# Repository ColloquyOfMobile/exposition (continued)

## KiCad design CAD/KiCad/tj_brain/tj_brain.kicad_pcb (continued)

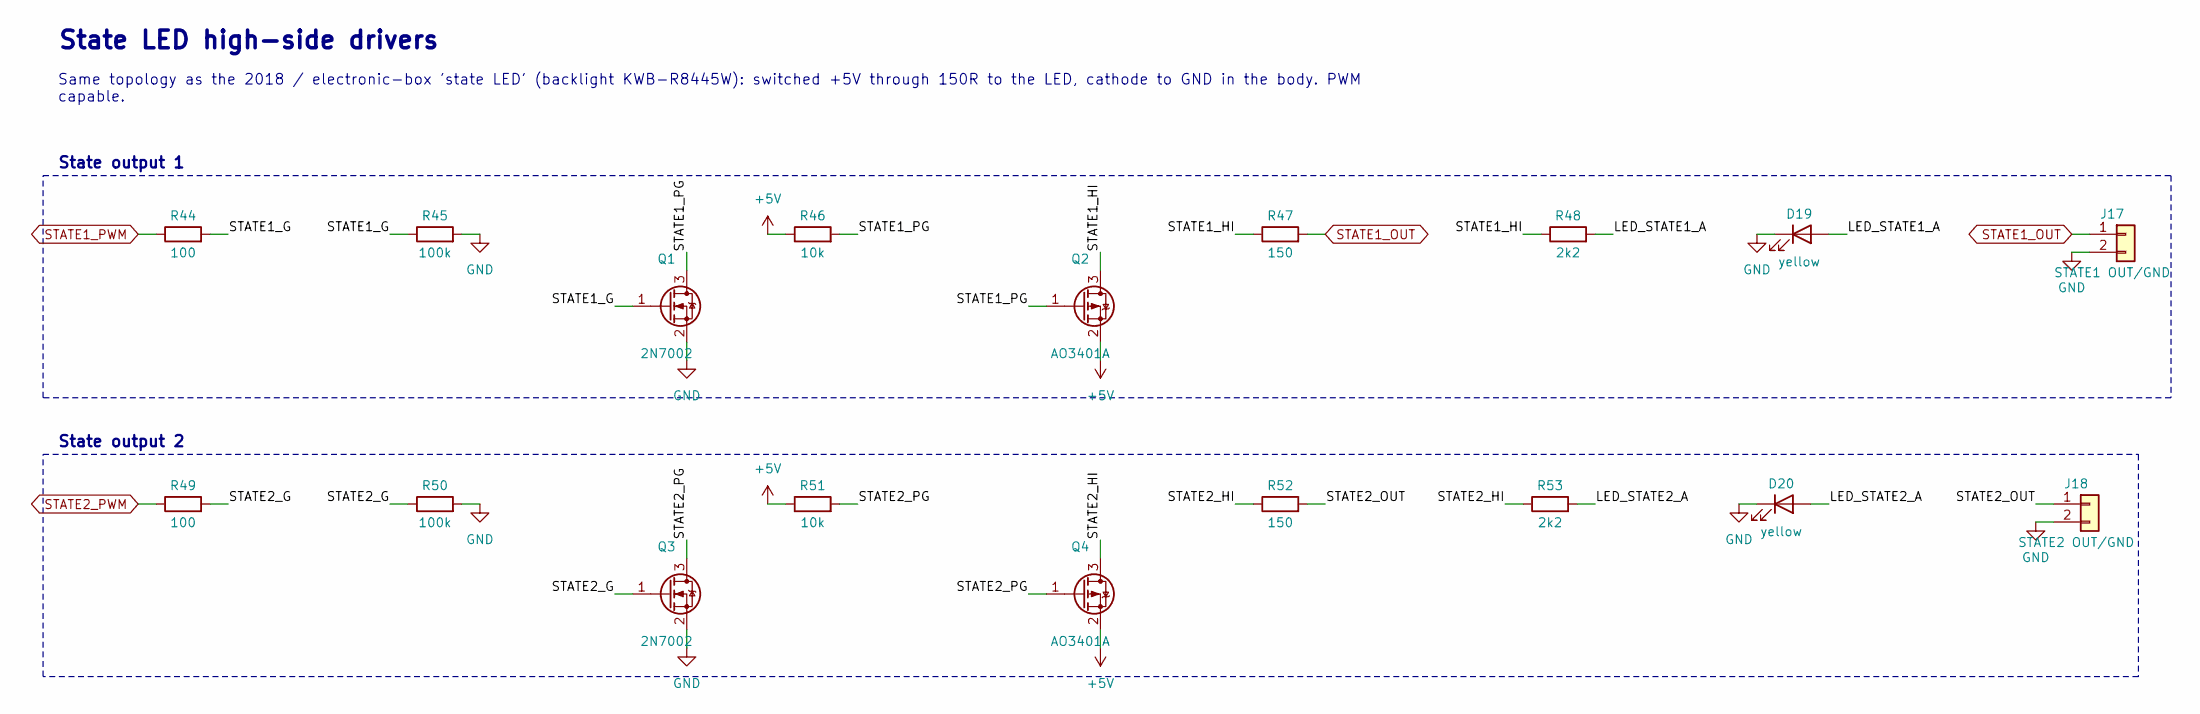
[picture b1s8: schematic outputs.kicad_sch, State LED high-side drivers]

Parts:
D19, D20: yellow; LED_0805_2012Metric_Pad1.15x1.40mm_HandSolder
J17: STATE1 OUT/GND; JST_XH_B2B-XH-A_1x02_P2.50mm_Vertical
J18: STATE2 OUT/GND; JST_XH_B2B-XH-A_1x02_P2.50mm_Vertical
Q1, Q3: 2N7002; SOT-23
Q2, Q4: AO3401A; SOT-23
R44, R49: 100; R_0805_2012Metric_Pad1.20x1.40mm_HandSolder
R45, R50: 100k; R_0805_2012Metric_Pad1.20x1.40mm_HandSolder
R46, R51: 10k; R_0805_2012Metric_Pad1.20x1.40mm_HandSolder
R47, R52: 150; R_1206_3216Metric_Pad1.30x1.75mm_HandSolder
R48, R53: 2k2; R_0805_2012Metric_Pad1.20x1.40mm_HandSolder

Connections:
+5V: Q2.2 (S), Q4.2 (S), R46.1, R51.1; also elsewhere on the board
GND: D19.1 (K), D20.1 (K), J17.2, J18.2, Q1.2 (S), Q3.2 (S), R45.2, R50.2; also elsewhere on the board
LED_STATE1_A: D19.2 (A), R48.2
LED_STATE2_A: D20.2 (A), R53.2
STATE1_G: Q1.1 (G), R44.2, R45.1
STATE1_HI: Q2.3 (D), R47.1, R48.1
STATE1_OUT: J17.1, R47.2; also elsewhere on the board
STATE1_PG: Q1.3 (D), Q2.1 (G), R46.2
STATE1_PWM: R44.1; also elsewhere on the board
STATE2_G: Q3.1 (G), R49.2, R50.1
STATE2_HI: Q4.3 (D), R52.1, R53.1
STATE2_OUT: J18.1, R52.2
STATE2_PG: Q3.3 (D), Q4.1 (G), R51.2
STATE2_PWM: R49.1; also elsewhere on the board

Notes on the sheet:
State LED high-side drivers
Same topology as the 2018 / electronic-box 'state LED' (backlight KWB-R8445W): switched +5V through 150R to the LED, cathode to GND in the body. PWM
capable.
State output 1
State output 2

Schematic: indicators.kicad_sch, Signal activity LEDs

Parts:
C25, C26: 100n; C_0805_2012Metric_Pad1.18x1.45mm_HandSolder
C27, C28, C29, C30, C31, C32, C33, C34: 47n; C_0805_2012Metric_Pad1.18x1.45mm_HandSolder
D21, D23, D25, D27, D29, D31, D33, D35: BAT54WS; D_SOD-323_HandSoldering
D22, D24, D26, D28: yellow; LED_0805_2012Metric_Pad1.15x1.40mm_HandSolder
D30, D32, D34, D36: orange; LED_0805_2012Metric_Pad1.15x1.40mm_HandSolder
J19: PROBE; PinHeader_1x01_P2.54mm_Vertical
R54: 100k; R_0805_2012Metric_Pad1.20x1.40mm_HandSolder
R55, R57, R58, R60, R61, R63, R64, R66, R67, R69, R70, R72, R73, R75, R78: 1k; R_0805_2012Metric_Pad1.20x1.40mm_HandSolder
R56, R59, R62, R65, R68, R71, R74, R77: 1M; R_0805_2012Metric_Pad1.20x1.40mm_HandSolder
R76: 4k7; R_0805_2012Metric_Pad1.20x1.40mm_HandSolder
U8, U9: 74HC14; SOIC-14_3.9x8.7mm_P1.27mm

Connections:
+3V3: C25.1, C26.1, R57.1, R60.1, R63.1, R66.1, R69.1, R71.2, R75.1, R78.1, U8.14 (VCC), U9.14 (VCC); also elsewhere on the board
AUDIO_PWM: R73.1; also elsewhere on the board
DXL_DIR: R67.1; also elsewhere on the board
DXL_RX: R70.1; also elsewhere on the board
GND: C25.2, C26.2, C27.2, C28.2, C29.2, C30.2, C31.2, C32.2, C33.2, C34.2, D32.1 (K), R54.2, R56.2, R59.2, R62.2, R65.2, R68.2, R74.2, R77.2, U8.7 (GND), U9.5, U9.7 (GND), U9.9, U9.11, U9.13; also elsewhere on the board
IND1_D: D21.2 (A), R55.2
IND1_K: D22.2 (A), R57.2
IND1_S: C27.1, D21.1 (K), R56.1, U8.1
IND1_Y: D22.1 (K), U8.2
IND2_D: D23.2 (A), R58.2
IND2_K: D24.2 (A), R60.2
IND2_S: C28.1, D23.1 (K), R59.1, U8.3
IND2_Y: D24.1 (K), U8.4
IND3_D: D25.2 (A), R61.2
IND3_K: D26.2 (A), R63.2
IND3_S: C29.1, D25.1 (K), R62.1, U8.5
IND3_Y: D26.1 (K), U8.6
IND4_D: D27.2 (A), R64.2
IND4_K: D28.2 (A), R66.2
IND4_S: C30.1, D27.1 (K), R65.1, U8.9
IND4_Y: D28.1 (K), U8.8
IND5_D: D29.2 (A), R67.2
IND5_K: D30.2 (A), R69.2
IND5_S: C31.1, D29.1 (K), R68.1, U8.11
IND5_Y: D30.1 (K), U8.10
IND6_D: D31.1 (K), R70.2
IND6_K: D32.2 (A), R72.2
IND6_S: C32.1, D31.2 (A), R71.1, U8.13
IND6_Y: R72.1, U8.12
IND7_D: D33.2 (A), R73.2
IND7_K: D34.2 (A), R75.2
IND7_S: C33.1, D33.1 (K), R74.1, U9.1
IND7_Y: D34.1 (K), U9.2
IND8_D: D35.2 (A), R76.2
IND8_K: D36.2 (A), R78.2
IND8_S: C34.1, D35.1 (K), R77.1, U9.3
IND8_Y: D36.1 (K), U9.4
NP1_3V: R55.1; also elsewhere on the board
NP2_3V: R58.1; also elsewhere on the board
NP3_3V: R61.1; also elsewhere on the board
NP4_3V: R64.1; also elsewhere on the board
PROBE: J19.1, R54.1, R76.1

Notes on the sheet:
Signal activity LEDs
Each signal is tapped through 1k + Schottky into 47n || 1M (~50 ms pulse stretcher) and drives a 74HC14 (3.3V) so that short NeoPixel / Dynamixel
bursts are visible. PROBE = free logic probe.
Schmitt inverters
Probe input
Indicator NP1
Indicator NP2
Indicator NP3
Indicator NP4
Indicator DXL TX
Indicator DXL BUS
Indicator TONE
Indicator PROBE

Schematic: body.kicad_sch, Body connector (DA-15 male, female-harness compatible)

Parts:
J20: BODY DA-15 male; DSUB-15_Male_Horizontal_P2.77x2.84mm_EdgePinOffset4.94mm_Ho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

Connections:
+5V_BODY: J20.15; also elsewhere on the board
+12V_BODY: J20.7; also elsewhere on the board
AUX_IN: J20.11 (P111); also elsewhere on the board
DXL_DATA: J20.14; also elsewhere on the board
GND: J20.0 (PAD), J20.8; also elsewhere on the board
LS1_IN: J20.5; also elsewhere on the board
LS2_IN: J20.1; also elsewhere on the board
LS3_IN: J20.2; also elsewhere on the board
LS4_IN: J20.3; also elsewhere on the board
MIC_IN: J20.6; also elsewhere on the board
NP1_OUT: J20.13; also elsewhere on the board
NP2_OUT: J20.9; also elsewhere on the board
SPK+: J20.12; also elsewhere on the board
SPK-: J20.4; also elsewhere on the board
STATE1_OUT: J20.10; also elsewhere on the board

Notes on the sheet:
Body connector (DA-15 male, female-harness compatible)
Pins 4,5,6,7,8,12,13,14,15 identical to the ZKM electronic box female D-subs (J1/J5), so existing female body harnesses plug in unchanged. Pins
1,2,3,9,10,11 add the male extras.
DA-15

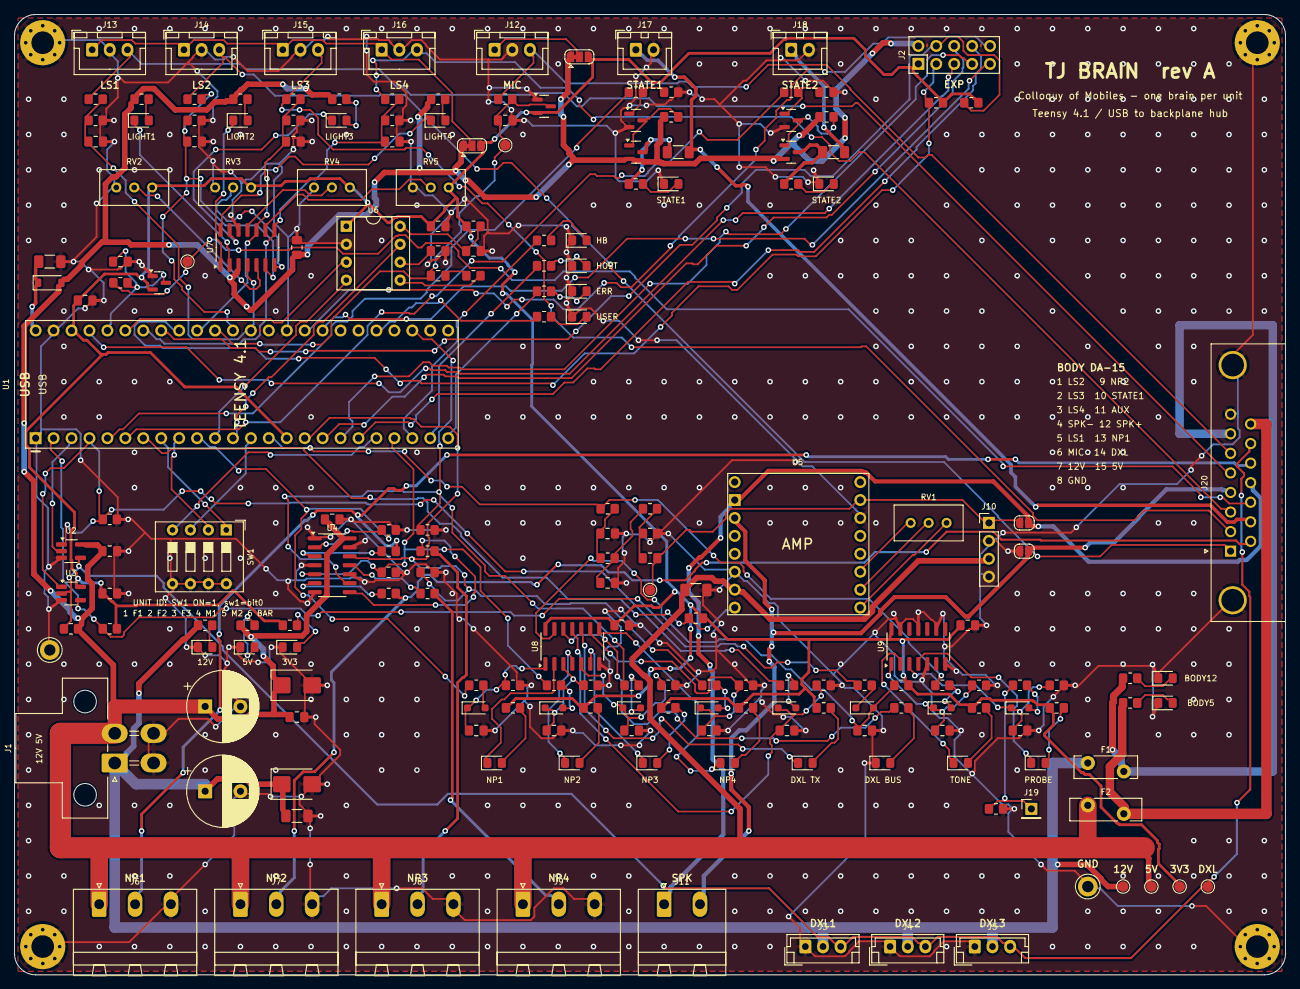
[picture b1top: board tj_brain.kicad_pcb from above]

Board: 2 copper layers, 180.0 x 136.0 mm, 206 parts (0 on the bottom side), 137 nets.

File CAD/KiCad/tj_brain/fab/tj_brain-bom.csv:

References,Qty,Value,Footprint,Manufacturer part / note,Populate,Description
C1,1,470u 25V,CP_Radial_D10.0mm_P5.00mm,,,
C2,1,100n,C_1206_3216Metric_Pad1.33x1.80mm_HandSolder,,,
C3,1,1000u 10V,CP_Radial_D10.0mm_P5.00mm,,,
"C4, C6, C7, C8, C9, C15, C16, C19, C25, C26",10,100n,C_0805_2012Metric_Pad1.18x1.45mm_HandSolder,,,
"C5, C13",2,10u,C_1206_3216Metric_Pad1.33x1.80mm_HandSolder,,,
"C10, C11",2,150n,C_0805_2012Metric_Pad1.18x1.45mm_HandSolder,,,
C12,1,1u,C_0805_2012Metric_Pad1.18x1.45mm_HandSolder,,,
C14,1,1n,C_0805_2012Metric_Pad1.18x1.45mm_HandSolder,,,
"C17, C20, C21, C22, C23, C24",6,10n,C_0805_2012Metric_Pad1.18x1.45mm_HandSolder,,,
C18,1,33p,C_0805_2012Metric_Pad1.18x1.45mm_HandSolder,,,
"C27, C28, C29, C30, C31, C32, C33, C34",8,47n,C_0805_2012Metric_Pad1.18x1.45mm_HandSolder,,,
D1,1,SMBJ15A,D_SMB,,,TVS 15V unidirectional
D2,1,SMBJ5.0A,D_SMB,,,TVS 5V unidirectional
D3,1,B5819W,D_SOD-123,,,Schottky 1A 40V; lets the Teensy VIN/VUSB link stay uncut
"D4, D7, D11",3,red,LED_0805_2012Metric_Pad1.15x1.40mm_HandSolder,,,
"D5, D6, D8, D9",4,green,LED_0805_2012Metric_Pad1.15x1.40mm_HandSolder,,,
D10,1,blue,LED_0805_2012Metric_Pad1.15x1.40mm_HandSolder,,,
"D12, D19, D20, D22, D24, D26, D28",7,yellow,LED_0805_2012Metric_Pad1.15x1.40mm_HandSolder,,,
"D13, D18",2,BAT54S,SOT-23,,,clamp 0..3.3V
"D14, D15, D16, D17",4,white,LED_0805_2012Metric_Pad1.15x1.40mm_HandSolder,,,
"D21, D23, D25, D27, D29, D31, D33, D35",8,BAT54WS,D_SOD-323_HandSoldering,,,
"D30, D32, D34, D36",4,orange,LED_0805_2012Metric_Pad1.15x1.40mm_HandSolder,,,
F1,1,MF-RHT300 3A,Fuse_Bourns_MF-RHT300,,,
F2,1,MF-RHT400 4A,Fuse_Bourns_MF-RHT400,,,
"H1, H2, H3, H4",4,M3,MountingHole_3.2mm_M3_Pad_Via,,,
J1,1,PWR IN Mini-Fit Jr,Molex_Mini-Fit_Jr_5569-04A1_2x02_P4.20mm_Horizontal,"Molex 39-30-1041 (5569-04A1, right angle)",,
J2,1,EXPANSION,PinHeader_2x05_P2.54mm_Vertical,,,
J3,1,DXL TTL 1,JST_EH_B3B-EH-A_1x03_P2.50mm_Vertical,,,
J4,1,DXL TTL 2,JST_EH_B3B-EH-A_1x03_P2.50mm_Vertical,,,
J5,1,DXL TTL 3,JST_EH_B3B-EH-A_1x03_P2.50mm_Vertical,,,
J6,1,NP1 5V/DIN/GND,"PhoenixContact_MSTBA_2,5_3-G-5,08_1x03_P5.08mm_Horizontal","Phoenix MSTBA 2,5/3-G-5,08 + MSTB 2,5/3-ST-5,08",,
J7,1,NP2 5V/DIN/GND,"PhoenixContact_MSTBA_2,5_3-G-5,08_1x03_P5.08mm_Horizontal","Phoenix MSTBA 2,5/3-G-5,08 + MSTB 2,5/3-ST-5,08",,
J8,1,NP3 5V/DIN/GND,"PhoenixContact_MSTBA_2,5_3-G-5,08_1x03_P5.08mm_Horizontal","Phoenix MSTBA 2,5/3-G-5,08 + MSTB 2,5/3-ST-5,08",,
J9,1,NP4 5V/DIN/GND,"PhoenixContact_MSTBA_2,5_3-G-5,08_1x03_P5.08mm_Horizontal","Phoenix MSTBA 2,5/3-G-5,08 + MSTB 2,5/3-ST-5,08",,
J10,1,EXT AMP,PinHeader_1x04_P2.54mm_Vertical,,,
J11,1,SPEAKER,"PhoenixContact_MSTBA_2,5_2-G-5,08_1x02_P5.08mm_Horizontal",,,
J12,1,MIC VCC/GND/OUT,JST_XH_B3B-XH-A_1x03_P2.50mm_Vertical,,,
J13,1,LS1 VCC/GND/SIG,JST_XH_B3B-XH-A_1x03_P2.50mm_Vertical,,,
J14,1,LS2 VCC/GND/SIG,JST_XH_B3B-XH-A_1x03_P2.50mm_Vertical,,,
J15,1,LS3 VCC/GND/SIG,JST_XH_B3B-XH-A_1x03_P2.50mm_Vertical,,,
J16,1,LS4 VCC/GND/SIG,JST_XH_B3B-XH-A_1x03_P2.50mm_Vertical,,,
J17,1,STATE1 OUT/GND,JST_XH_B2B-XH-A_1x02_P2.50mm_Vertical,,,
J18,1,STATE2 OUT/GND,JST_XH_B2B-XH-A_1x02_P2.50mm_Vertical,,,
J19,1,PROBE,PinHeader_1x01_P2.54mm_Vertical,,,
J20,1,BODY DA-15 male,DSUB-15_Male_Horizontal_P2.77x2.84mm_EdgePinOffset4.94mm_Housed_MountingHolesOffset7.48mm,,,
JP1,1,LINE->SPK+,SolderJumper-2_P1.3mm_Open_RoundedPad1.0x1.5mm,,,close (and leave U5 out) to send line level on the D-sub speaker pins
JP2,1,GND->SPK-,SolderJumper-2_P1.3mm_Open_RoundedPad1.0x1.5mm,,,
JP3,1,MIC VCC 5V|3V3,SolderJumper-3_P1.3mm_Bridged12_RoundedPad1.0x1.5mm,,,
JP4,1,LS VCC 5V|3V3,SolderJumper-3_P1.3mm_Bridged12_RoundedPad1.0x1.5mm,,,
"Q1, Q3",2,2N7002,SOT-23,,,
"Q2, Q4",2,AO3401A,SOT-23,,,
"R1, R4, R12, R13, R14, R31, R34, R37, R40, R46, R51",11,10k,R_0805_2012Metric_Pad1.20x1.40mm_HandSolder,,,bus pull-up (as ROBOTIS reference); default = receive
"R2, R5, R33, R36, R39, R42, R48, R53",8,2k2,R_0805_2012Metric_Pad1.20x1.40mm_HandSolder,,,
"R3, R6, R8, R9, R28, R43, R55, R57, R58, R60, R61, R63, R64, R66, R67, R69, R70, R72, R73, R75, R78",21,1k,R_0805_2012Metric_Pad1.20x1.40mm_HandSolder,,,
"R7, R16, R18, R20, R22",5,330,R_0805_2012Metric_Pad1.20x1.40mm_HandSolder,,,
"R10, R11",2,2k2,R_0805_2012Metric_Pad1.20x1.40mm_HandSolder,,DNP,optional I2C pull-up
"R15, R17, R19, R21, R27, R45, R50, R54",8,100k,R_0805_2012Metric_Pad1.20x1.40mm_HandSolder,,,amp enabled by default; keeps strip quiet while Teensy boots
"R23, R24",2,1k2,R_0805_2012Metric_Pad1.20x1.40mm_HandSolder,,,
"R25, R29",2,22k,R_0805_2012Metric_Pad1.20x1.40mm_HandSolder,,,
R26,1,6k8,R_0805_2012Metric_Pad1.20x1.40mm_HandSolder,,,
R30,1,200k,R_0805_2012Metric_Pad1.20x1.40mm_HandSolder,,,
"R32, R35, R38, R41",4,18k,R_0805_2012Metric_Pad1.20x1.40mm_HandSolder,,,
"R44, R49",2,100,R_0805_2012Metric_Pad1.20x1.40mm_HandSolder,,,
"R47, R52",2,150,R_1206_3216Metric_Pad1.30x1.75mm_HandSolder,,,LED current limit (0R for self-limited loads)
"R56, R59, R62, R65, R68, R71, R74, R77",8,1M,R_0805_2012Metric_Pad1.20x1.40mm_HandSolder,,,
R76,1,4k7,R_0805_2012Metric_Pad1.20x1.40mm_HandSolder,,,
RV1,1,10k VOLUME,Potentiometer_Bourns_3296W_Vertical,,,
"RV2, RV3, RV4, RV5",4,10k,Potentiometer_Bourns_3296W_Vertical,,,
SW1,1,UNIT ID,SW_DIP_SPSTx04_Slide_9.78x12.34mm_W7.62mm_P2.54mm,,,
"TP1, TP2",2,GND,TestPoint_Keystone_5005-5009_Compact,,,
TP3,1,+12V,TestPoint_Pad_D1.5mm,,,
TP4,1,+5V,TestPoint_Pad_D1.5mm,,,
TP5,1,+3V3,TestPoint_Pad_D1.5mm,,,
TP6,1,DXL_DATA,TestPoint_Pad_D1.5mm,,,
TP7,1,AUDIO,TestPoint_Pad_D1.5mm,,,
TP8,1,MIC,TestPoint_Pad_D1.5mm,,,
TP9,1,AUX,TestPoint_Pad_D1.5mm,,,
U1,1,Teensy 4.1,Teensy41_Socket,PJRC Teensy 4.1 + 2x 1x24 female header 2.54mm,,
U2,1,74AHCT1G126,SOT-23-5_HandSoldering,,,
U3,1,74LVC1G125,SOT-23-5_HandSoldering,,,
U4,1,74AHCT125,SOIC-14_3.9x8.7mm_P1.27mm,,,use 74AHCT125 (TTL thresholds @5V)
U5,1,SparkFun BOB-11044,SparkFun_TPA2005D1_Breakout,,,
U6,1,MSGEQ7,DIP-8_W7.62mm_Socket,,,
U7,1,LM339,SOIC-14_3.9x8.7mm_P1.27mm,,,
"U8, U9",2,74HC14,SOIC-14_3.9x8.7mm_P1.27mm,,,

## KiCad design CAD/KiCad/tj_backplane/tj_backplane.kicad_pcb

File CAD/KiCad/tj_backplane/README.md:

# TJ Backplane – 12V / 5V splitter (+ USB hub supply)

The backplane no longer carries signals between units. It now only splits power to the
brain boards:

* **12V** (Dynamixels) and **5V** (NeoPixels and logic) from two PSUs go to up to
  seven TJ Brain boards: F1, F2, F3, M1, M2, BAR and one spare.
* **USB** goes through a commercial 7-port *powered* USB 2.0 hub next to the backplane.
  The backplane powers the hub from its `HUB 5V OUT` terminal (fused). Each brain gets
  its own USB A to micro-B cable into the Teensy. The computer then sees six
  independent serial ports, and each Teensy reports its unit ID.

There is no hub chip on this board. I could not get a hub IC datasheet (FE1.1s etc.)
from inside the design sandbox, and a high-speed USB hub designed from memory would be
a weak point. A good industrial hub is cheap and proven.

## Board

200 × 85 mm, 2 layers. **Order it with 2 oz copper**: the 5V input carries up to about
25 A. The top layer has a solid +5V plane from the input to all the 5V fuses; the
bottom layer is GND.

| Ref | Function |
|-----|----------|
| J1 | 12V in, Phoenix MKDS 1,5/2-5.08 (1 = +12V, 2 = GND), ≤ 10 A |
| J2 | 5V in, Phoenix MKDS 1,5/4-5.08 (1, 2 = +5V; 3, 4 = GND), two poles in parallel, ≤ 25 A |
| J3 | HUB 5V OUT, MKDS 2p (1 = +5V, 2 = GND), PTC 3 A. Make a pigtail to the hub's DC plug |
| J4–J10 | outputs F1 F2 F3 M1 M2 BAR SPARE, Molex Mini-Fit Jr 5566-04A vertical |
| per output | PTC 3 A (MF-RHT300) on 12V and 5 A (MF-RHT500) on 5V, one LED per rail after its fuse |
| D1/D2, C1/C2 | input TVS (SMBJ15A / SMBJ5.0A) and bulk capacitors |

### Output / brain cable

Make each cable with a Mini-Fit Jr receptacle housing (Molex 39-01-2040, 5557-04R) at
**both** ends, crimp terminals 39-00-0039, and 18 AWG wire wired **pin to pin**:

| Pin | Wire | Signal |
|----:|------|--------|
| 1 | red | +12V |
| 2 | orange | +5V |
| 3 | black | GND |
| 4 | black | GND |

The brain uses the right-angle header 5569-04A1 with the same numbering.

An LED that is off means that rail is missing or its PTC has tripped. Unplug the load,
wait a few seconds, and the PTC resets.

## Files

`tj_backplane.kicad_sch`, `tj_backplane.kicad_pcb`, and `fab/` (Gerbers + drill zip,
BOM, positions, schematic PDF, renders). The board is generated by
`../generator/build_backplane.py`.

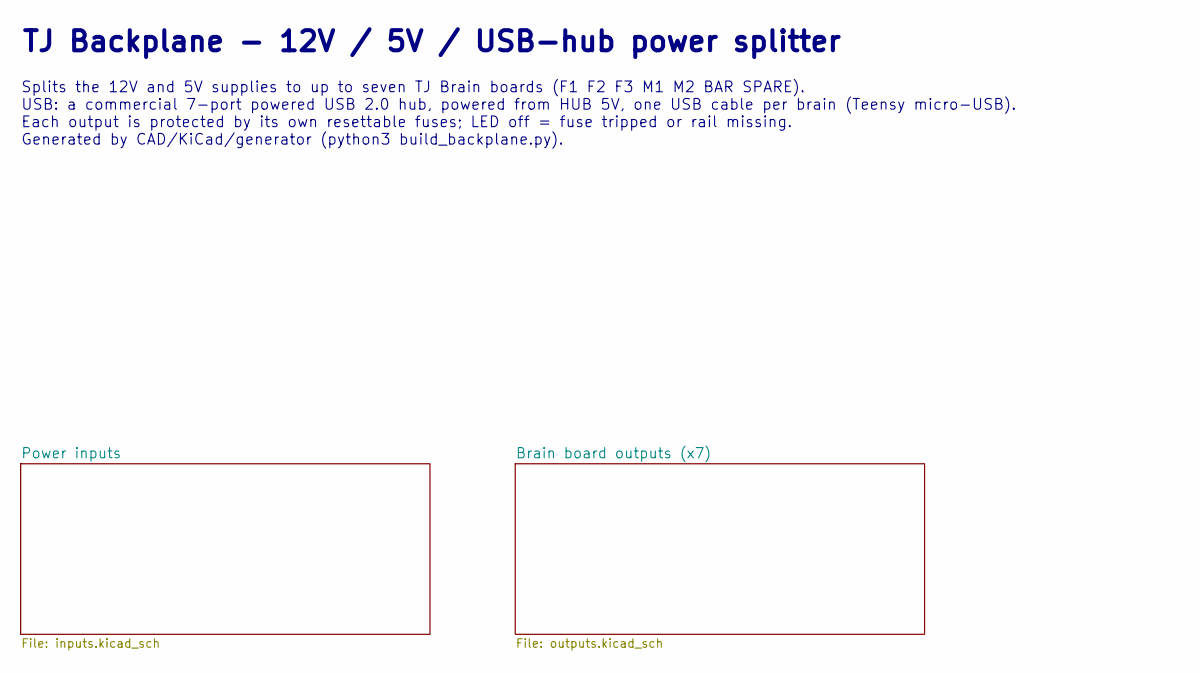
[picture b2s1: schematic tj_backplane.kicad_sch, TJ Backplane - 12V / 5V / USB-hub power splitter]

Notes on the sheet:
TJ Backplane - 12V / 5V / USB-hub power splitter
Splits the 12V and 5V supplies to up to seven TJ Brain boards (F1 F2 F3 M1 M2 BAR SPARE).
USB: a commercial 7-port powered USB 2.0 hub, powered from HUB 5V, one USB cable per brain (Teensy micro-USB).
Each output is protected by its own resettable fuses; LED off = fuse tripped or rail missing.
Generated by CAD/KiCad/generator (python3 build_backplane.py).

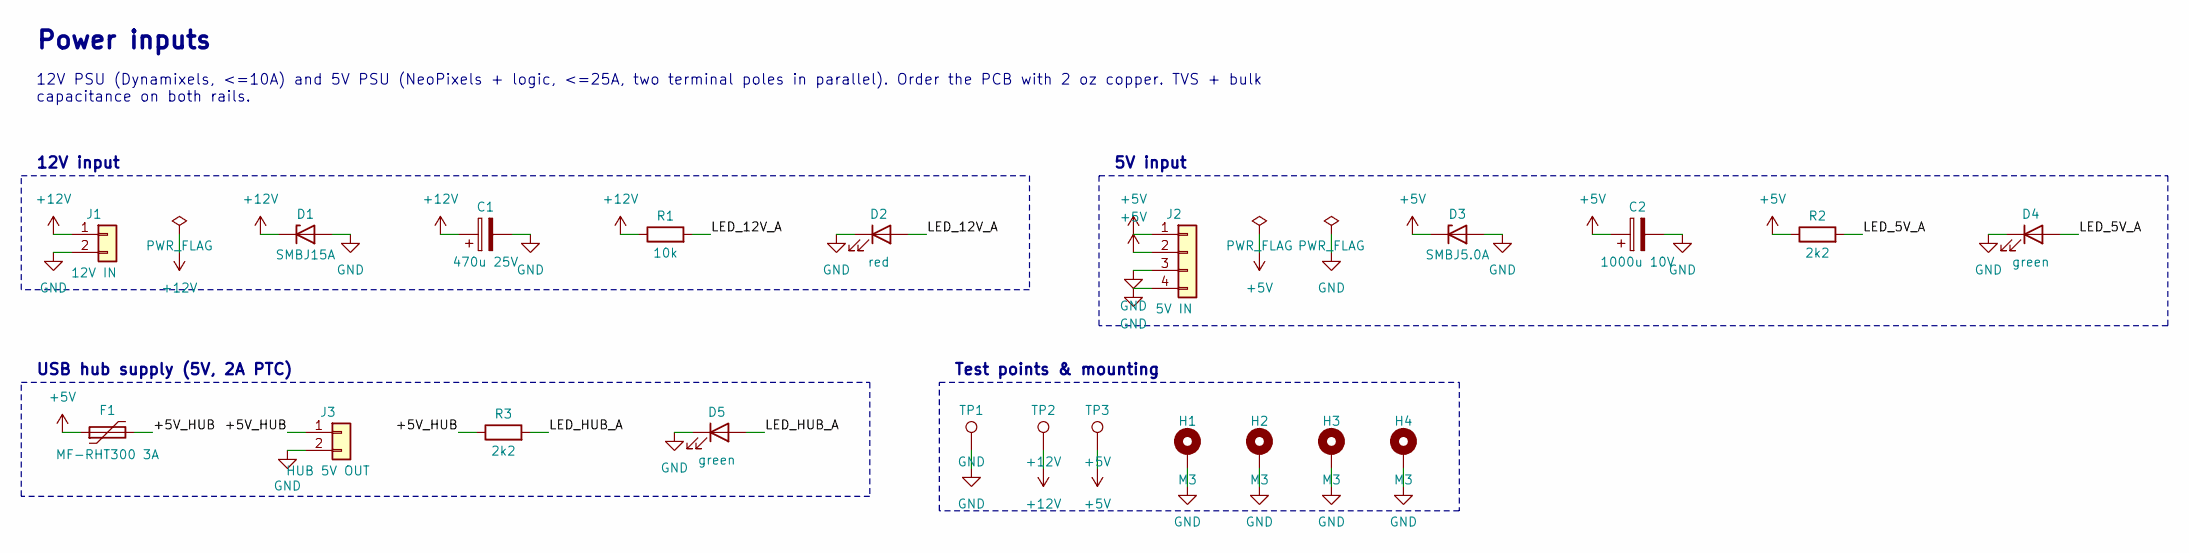
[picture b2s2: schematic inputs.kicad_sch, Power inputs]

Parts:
C1: 470u 25V; CP_Radial_D10.0mm_P5.00mm
C2: 1000u 10V; CP_Radial_D10.0mm_P5.00mm
D1: SMBJ15A; D_SMB
D2: red; LED_0805_2012Metric_Pad1.15x1.40mm_HandSolder
D3: SMBJ5.0A; D_SMB
D4, D5: green; LED_0805_2012Metric_Pad1.15x1.40mm_HandSolder
F1: MF-RHT300 3A; Fuse_Bourns_MF-RHT300
H1, H2, H3, H4: M3; MountingHole_3.2mm_M3_Pad_Via
J1: 12V IN; TerminalBlock_Phoenix_MKDS-1,5-2-5.08_1x02_P5.08mm_Horizont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
J2: 5V IN; TerminalBlock_Phoenix_MKDS-1,5-4-5.08_1x04_P5.08mm_Horizont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
J3: HUB 5V OUT; TerminalBlock_Phoenix_MKDS-1,5-2-5.08_1x02_P5.08mm_Horizont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
R1: 10k; R_0805_2012Metric_Pad1.20x1.40mm_HandSolder
R2, R3: 2k2; R_0805_2012Metric_Pad1.20x1.40mm_HandSolder
TP1: GND; TestPoint_Keystone_5005-5009_Compact
TP2: +12V; TestPoint_Pad_D1.5mm
TP3: +5V; TestPoint_Pad_D1.5mm

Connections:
+5V: C2.1, D3.1 (K), F1.1, J2.1, J2.2, R2.1, TP3.1; also elsewhere on the board
+5V_HUB: F1.2, J3.1, R3.1
+12V: C1.1, D1.1 (K), J1.1, R1.1, TP2.1; also elsewhere on the board
GND: C1.2, C2.2, D1.2 (A), D2.1 (K), D3.2 (A), D4.1 (K), D5.1 (K), H1.1, H2.1, H3.1, H4.1, J1.2, J2.3, J2.4, J3.2, TP1.1; also elsewhere on the board
LED_5V_A: D4.2 (A), R2.2
LED_12V_A: D2.2 (A), R1.2
LED_HUB_A: D5.2 (A), R3.2

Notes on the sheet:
Power inputs
12V PSU (Dynamixels, <=10A) and 5V PSU (NeoPixels + logic, <=25A, two terminal poles in parallel). Order the PCB with 2 oz copper. TVS + bulk
capacitance on both rails.
12V input
5V input
USB hub supply (5V, 2A PTC)
Test points & mounting

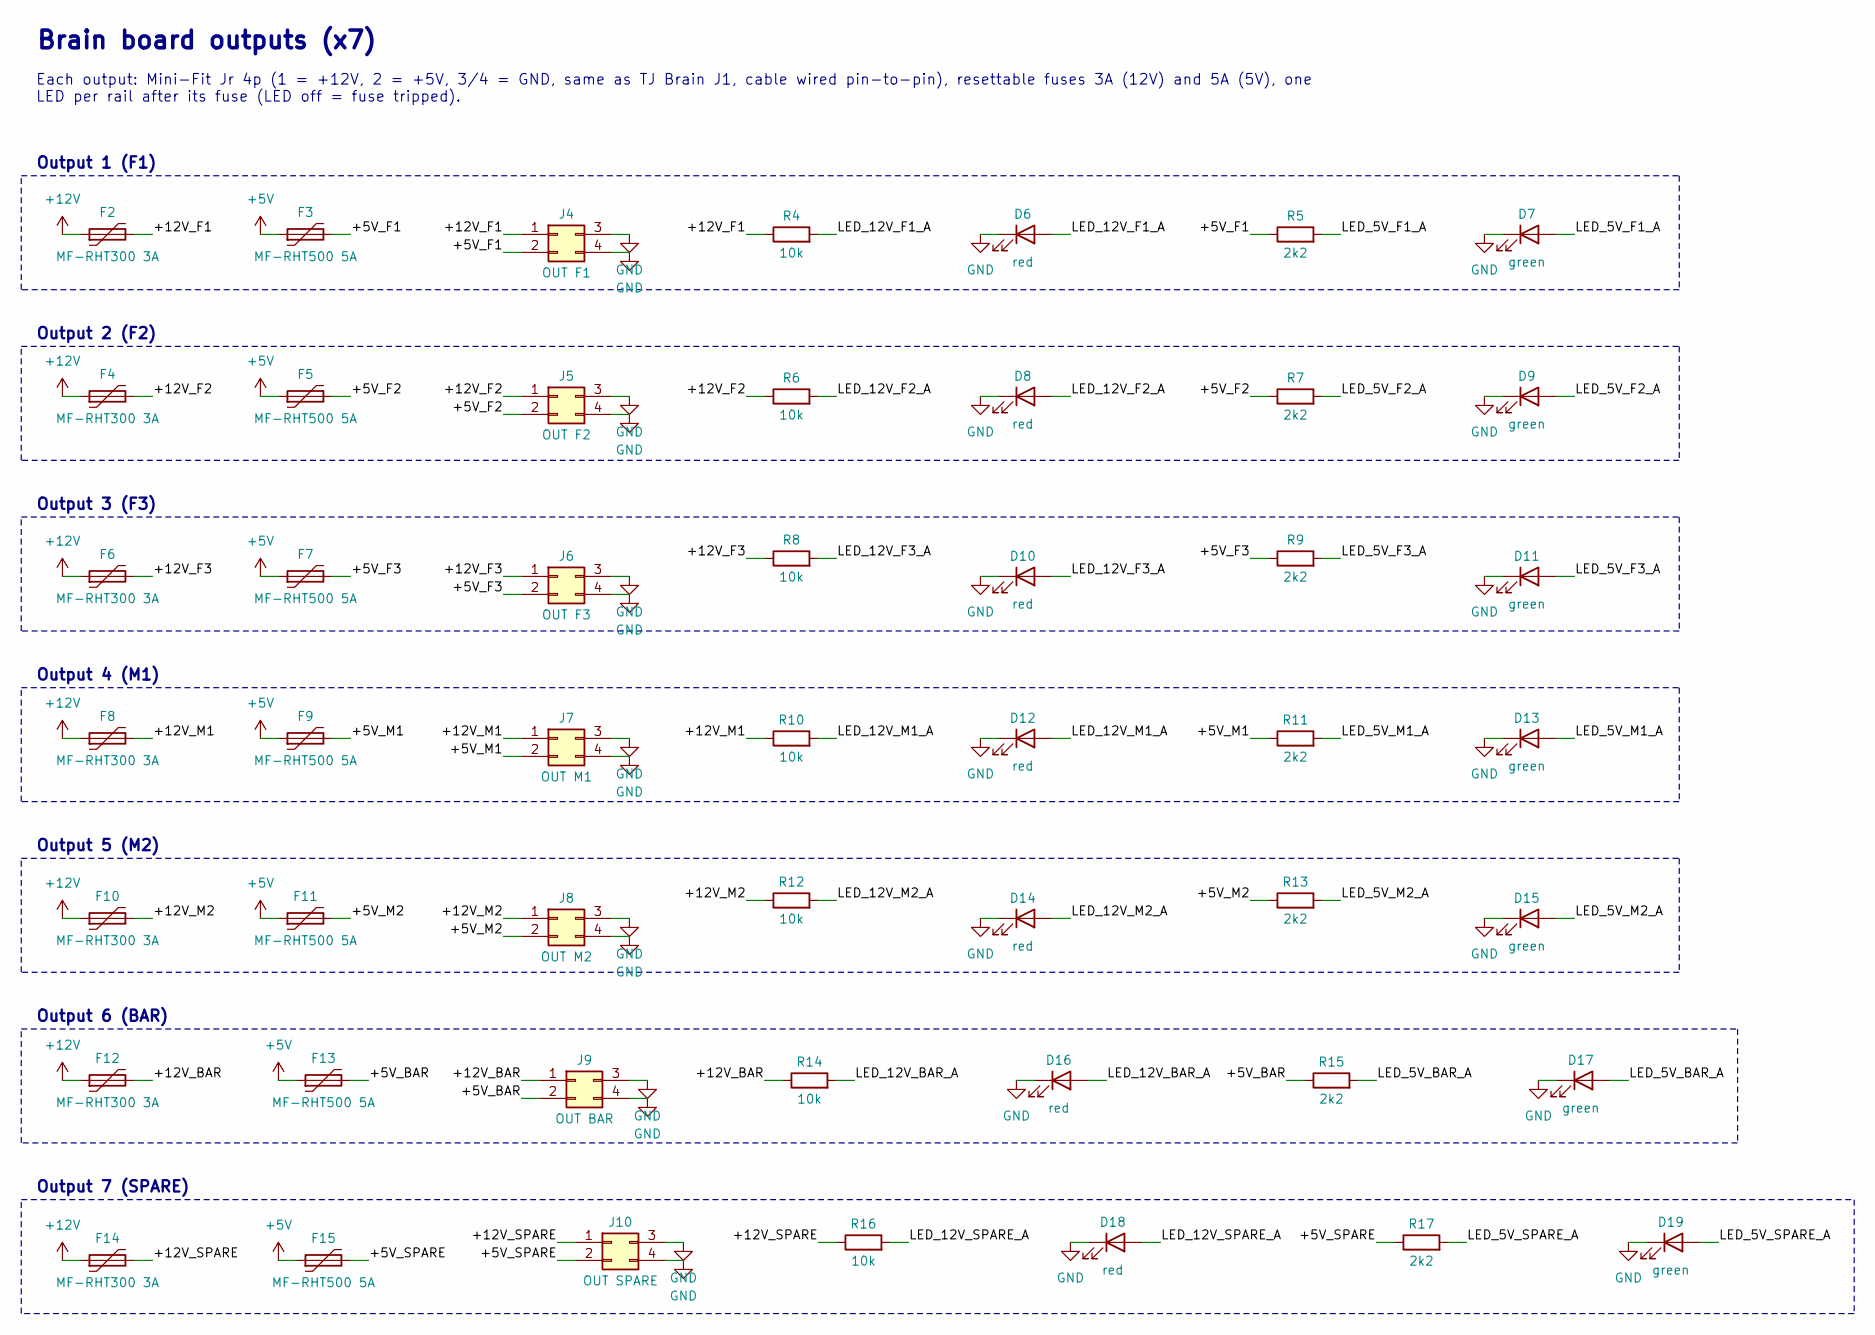
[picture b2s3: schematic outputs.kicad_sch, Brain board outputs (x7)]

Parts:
D6, D8, D10, D12, D14, D16, D18: red; LED_0805_2012Metric_Pad1.15x1.40mm_HandSolder
D7, D9, D11, D13, D15, D17, D19: green; LED_0805_2012Metric_Pad1.15x1.40mm_HandSolder
F2, F4, F6, F8, F10, F12, F14: MF-RHT300 3A; Fuse_Bourns_MF-RHT300
F3, F5, F7, F9, F11, F13, F15: MF-RHT500 5A; Fuse_Bourns_MF-RHT500
J4: OUT F1; Molex_Mini-Fit_Jr_5566-04A_2x02_P4.20mm_Vertical; MPN Molex 39-30-1040 (5566-04A)
J5: OUT F2; Molex_Mini-Fit_Jr_5566-04A_2x02_P4.20mm_Vertical; MPN Molex 39-30-1040 (5566-04A)
J6: OUT F3; Molex_Mini-Fit_Jr_5566-04A_2x02_P4.20mm_Vertical; MPN Molex 39-30-1040 (5566-04A)
J7: OUT M1; Molex_Mini-Fit_Jr_5566-04A_2x02_P4.20mm_Vertical; MPN Molex 39-30-1040 (5566-04A)
J8: OUT M2; Molex_Mini-Fit_Jr_5566-04A_2x02_P4.20mm_Vertical; MPN Molex 39-30-1040 (5566-04A)
J9: OUT BAR; Molex_Mini-Fit_Jr_5566-04A_2x02_P4.20mm_Vertical; MPN Molex 39-30-1040 (5566-04A)
J10: OUT SPARE; Molex_Mini-Fit_Jr_5566-04A_2x02_P4.20mm_Vertical; MPN Molex 39-30-1040 (5566-04A)
R4, R6, R8, R10, R12, R14, R16: 10k; R_0805_2012Metric_Pad1.20x1.40mm_HandSolder
R5, R7, R9, R11, R13, R15, R17: 2k2; R_0805_2012Metric_Pad1.20x1.40mm_HandSolder

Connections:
+5V: F3.1, F5.1, F7.1, F9.1, F11.1, F13.1, F15.1; also elsewhere on the board
+5V_BAR: F13.2, J9.2, R15.1
+5V_F1: F3.2, J4.2, R5.1
+5V_F2: F5.2, J5.2, R7.1
+5V_F3: F7.2, J6.2, R9.1
+5V_M1: F9.2, J7.2, R11.1
+5V_M2: F11.2, J8.2, R13.1
+5V_SPARE: F15.2, J10.2, R17.1
+12V: F2.1, F4.1, F6.1, F8.1, F10.1, F12.1, F14.1; also elsewhere on the board
+12V_BAR: F12.2, J9.1, R14.1
+12V_F1: F2.2, J4.1, R4.1
+12V_F2: F4.2, J5.1, R6.1
+12V_F3: F6.2, J6.1, R8.1
+12V_M1: F8.2, J7.1, R10.1
+12V_M2: F10.2, J8.1, R12.1
+12V_SPARE: F14.2, J10.1, R16.1
GND: D6.1 (K), D7.1 (K), D8.1 (K), D9.1 (K), D10.1 (K), D11.1 (K), D12.1 (K), D13.1 (K), D14.1 (K), D15.1 (K), D16.1 (K), D17.1 (K), D18.1 (K), D19.1 (K), J4.3, J4.4, J5.3, J5.4, J6.3, J6.4, J7.3, J7.4, J8.3, J8.4, J9.3, J9.4, J10.3, J10.4; also elsewhere on the board
LED_5V_BAR_A: D17.2 (A), R15.2
LED_5V_F1_A: D7.2 (A), R5.2
LED_5V_F2_A: D9.2 (A), R7.2
LED_5V_F3_A: D11.2 (A), R9.2
LED_5V_M1_A: D13.2 (A), R11.2
LED_5V_M2_A: D15.2 (A), R13.2
LED_5V_SPARE_A: D19.2 (A), R17.2
LED_12V_BAR_A: D16.2 (A), R14.2
LED_12V_F1_A: D6.2 (A), R4.2
LED_12V_F2_A: D8.2 (A), R6.2
LED_12V_F3_A: D10.2 (A), R8.2
LED_12V_M1_A: D12.2 (A), R10.2
LED_12V_M2_A: D14.2 (A), R12.2
LED_12V_SPARE_A: D18.2 (A), R16.2

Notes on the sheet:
Brain board outputs (x7)
Each output: Mini-Fit Jr 4p (1 = +12V, 2 = +5V, 3/4 = GND, same as TJ Brain J1, cable wired pin-to-pin), resettable fuses 3A (12V) and 5A (5V), one
LED per rail after its fuse (LED off = fuse tripped).
Output 1 (F1)
Output 2 (F2)
Output 3 (F3)
Output 4 (M1)
Output 5 (M2)
Output 6 (BAR)
Output 7 (SPARE)

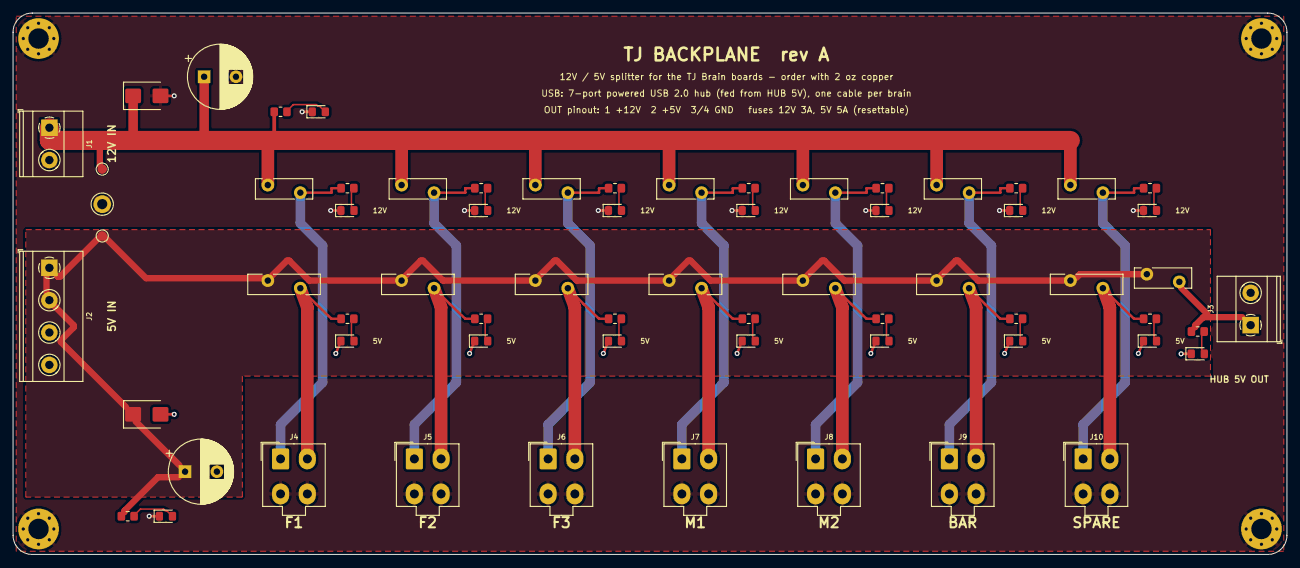
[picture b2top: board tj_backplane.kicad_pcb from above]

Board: 2 copper layers, 200.0 x 85.0 mm, 70 parts (0 on the bottom side), 35 nets.

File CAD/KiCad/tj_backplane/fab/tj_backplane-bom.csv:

References,Qty,Value,Footprint,Manufacturer part / note,Populate,Description
C1,1,470u 25V,CP_Radial_D10.0mm_P5.00mm,,,
C2,1,1000u 10V,CP_Radial_D10.0mm_P5.00mm,,,
D1,1,SMBJ15A,D_SMB,,,TVS 15V unidirectional
"D2, D6, D8, D10, D12, D14, D16, D18",8,red,LED_0805_2012Metric_Pad1.15x1.40mm_HandSolder,,,
D3,1,SMBJ5.0A,D_SMB,,,TVS 5V unidirectional
"D4, D5, D7, D9, D11, D13, D15, D17, D19",9,green,LED_0805_2012Metric_Pad1.15x1.40mm_HandSolder,,,
"F1, F2, F4, F6, F8, F10, F12, F14",8,MF-RHT300 3A,Fuse_Bourns_MF-RHT300,,,
"F3, F5, F7, F9, F11, F13, F15",7,MF-RHT500 5A,Fuse_Bourns_MF-RHT500,,,
"H1, H2, H3, H4",4,M3,MountingHole_3.2mm_M3_Pad_Via,,,
J1,1,12V IN,"TerminalBlock_Phoenix_MKDS-1,5-2-5.08_1x02_P5.08mm_Horizontal",,,
J2,1,5V IN,"TerminalBlock_Phoenix_MKDS-1,5-4-5.08_1x04_P5.08mm_Horizontal",,,
J3,1,HUB 5V OUT,"TerminalBlock_Phoenix_MKDS-1,5-2-5.08_1x02_P5.08mm_Horizontal",,,
J4,1,OUT F1,Molex_Mini-Fit_Jr_5566-04A_2x02_P4.20mm_Vertical,Molex 39-30-1040 (5566-04A),,
J5,1,OUT F2,Molex_Mini-Fit_Jr_5566-04A_2x02_P4.20mm_Vertical,Molex 39-30-1040 (5566-04A),,
J6,1,OUT F3,Molex_Mini-Fit_Jr_5566-04A_2x02_P4.20mm_Vertical,Molex 39-30-1040 (5566-04A),,
J7,1,OUT M1,Molex_Mini-Fit_Jr_5566-04A_2x02_P4.20mm_Vertical,Molex 39-30-1040 (5566-04A),,
J8,1,OUT M2,Molex_Mini-Fit_Jr_5566-04A_2x02_P4.20mm_Vertical,Molex 39-30-1040 (5566-04A),,
J9,1,OUT BAR,Molex_Mini-Fit_Jr_5566-04A_2x02_P4.20mm_Vertical,Molex 39-30-1040 (5566-04A),,
J10,1,OUT SPARE,Molex_Mini-Fit_Jr_5566-04A_2x02_P4.20mm_Vertical,Molex 39-30-1040 (5566-04A),,
"R1, R4, R6, R8, R10, R12, R14, R16",8,10k,R_0805_2012Metric_Pad1.20x1.40mm_HandSolder,,,
"R2, R3, R5, R7, R9, R11, R13, R15, R17",9,2k2,R_0805_2012Metric_Pad1.20x1.40mm_HandSolder,,,
TP1,1,GND,TestPoint_Keystone_5005-5009_Compact,,,
TP2,1,+12V,TestPoint_Pad_D1.5mm,,,
TP3,1,+5V,TestPoint_Pad_D1.5mm,,,

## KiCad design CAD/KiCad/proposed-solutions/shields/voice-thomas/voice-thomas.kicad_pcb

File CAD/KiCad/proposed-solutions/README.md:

# Editable designs

Current replacement designs and alternatives live here. Only the seven boards listed
in [the electronics index](../README.md) are selected for manufacture. In particular,
`electronic box v2` and `thomas-or-teensy` are alternative main-board studies.

Use `shields/microphone-flex` for the production microphone holder. Original boards
are preserved under `../old-reference`; purchased-module references are under
`../provided-elements`. Generated order files are under `../production`.

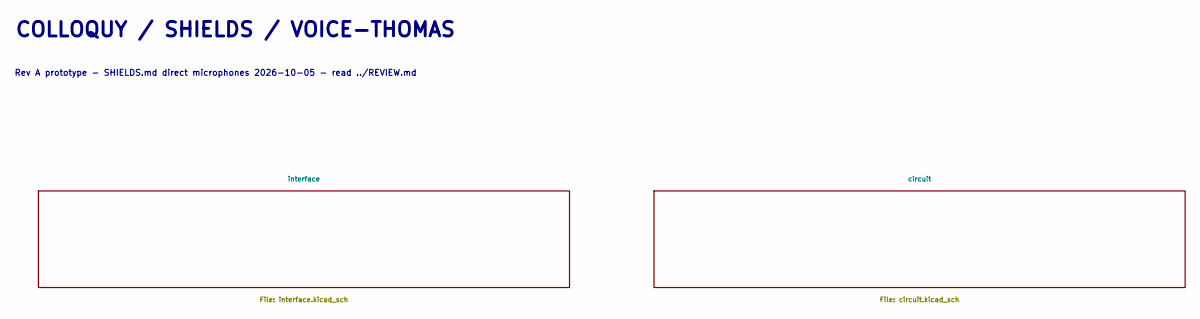
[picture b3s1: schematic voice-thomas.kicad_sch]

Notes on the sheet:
COLLOQUY / SHIELDS / VOICE-THOMAS
Rev A prototype - SHIELDS.md direct microphones 2026-10-05 - read ../REVIEW.md

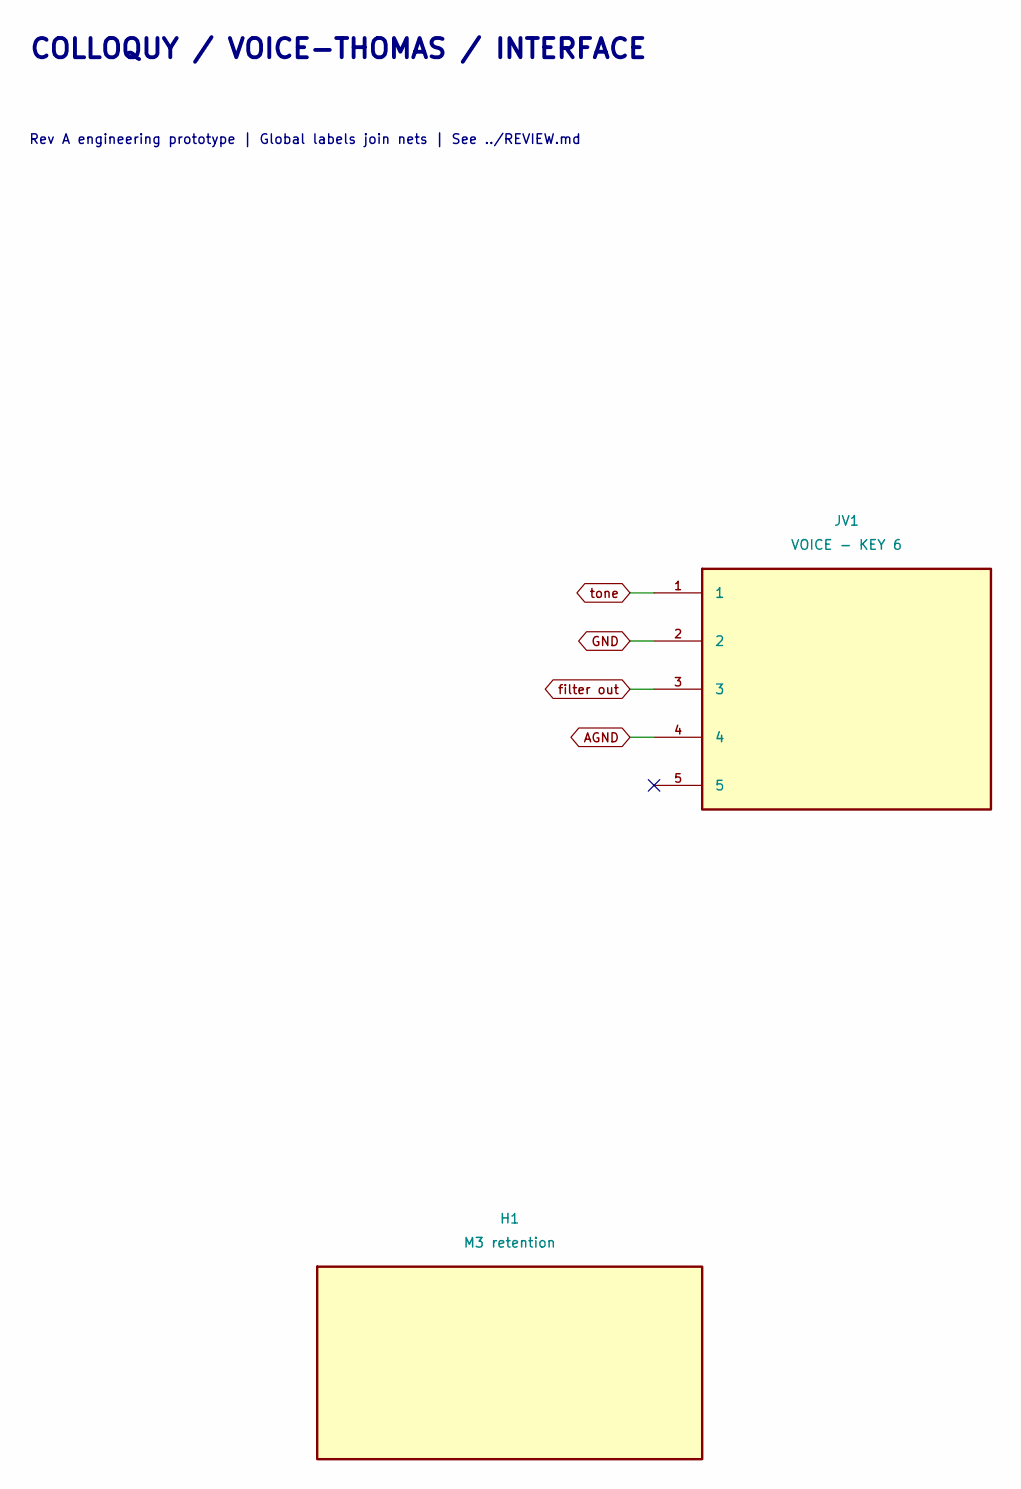
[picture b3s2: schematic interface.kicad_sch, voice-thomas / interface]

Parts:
H1: M3 retention; MountingHole_3.2mm_M3
JV1: VOICE - KEY 6; Socket_2x03_Key6

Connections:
AGND: JV1.4; also elsewhere on the board
GND: JV1.2; also elsewhere on the board
filter out: JV1.3; also elsewhere on the board
tone: JV1.1; also elsewhere on the board

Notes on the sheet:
COLLOQUY / VOICE-THOMAS / INTERFACE
Rev A engineering prototype | Global labels join nets | See ../REVIEW.md
